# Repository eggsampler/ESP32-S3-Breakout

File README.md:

View this project on [CADLAB.io](https://cadlab.io/project/26428). 

# ESP32-S3-Breakout-
A minimal breakout board for the ESP32-S3-WROOM module

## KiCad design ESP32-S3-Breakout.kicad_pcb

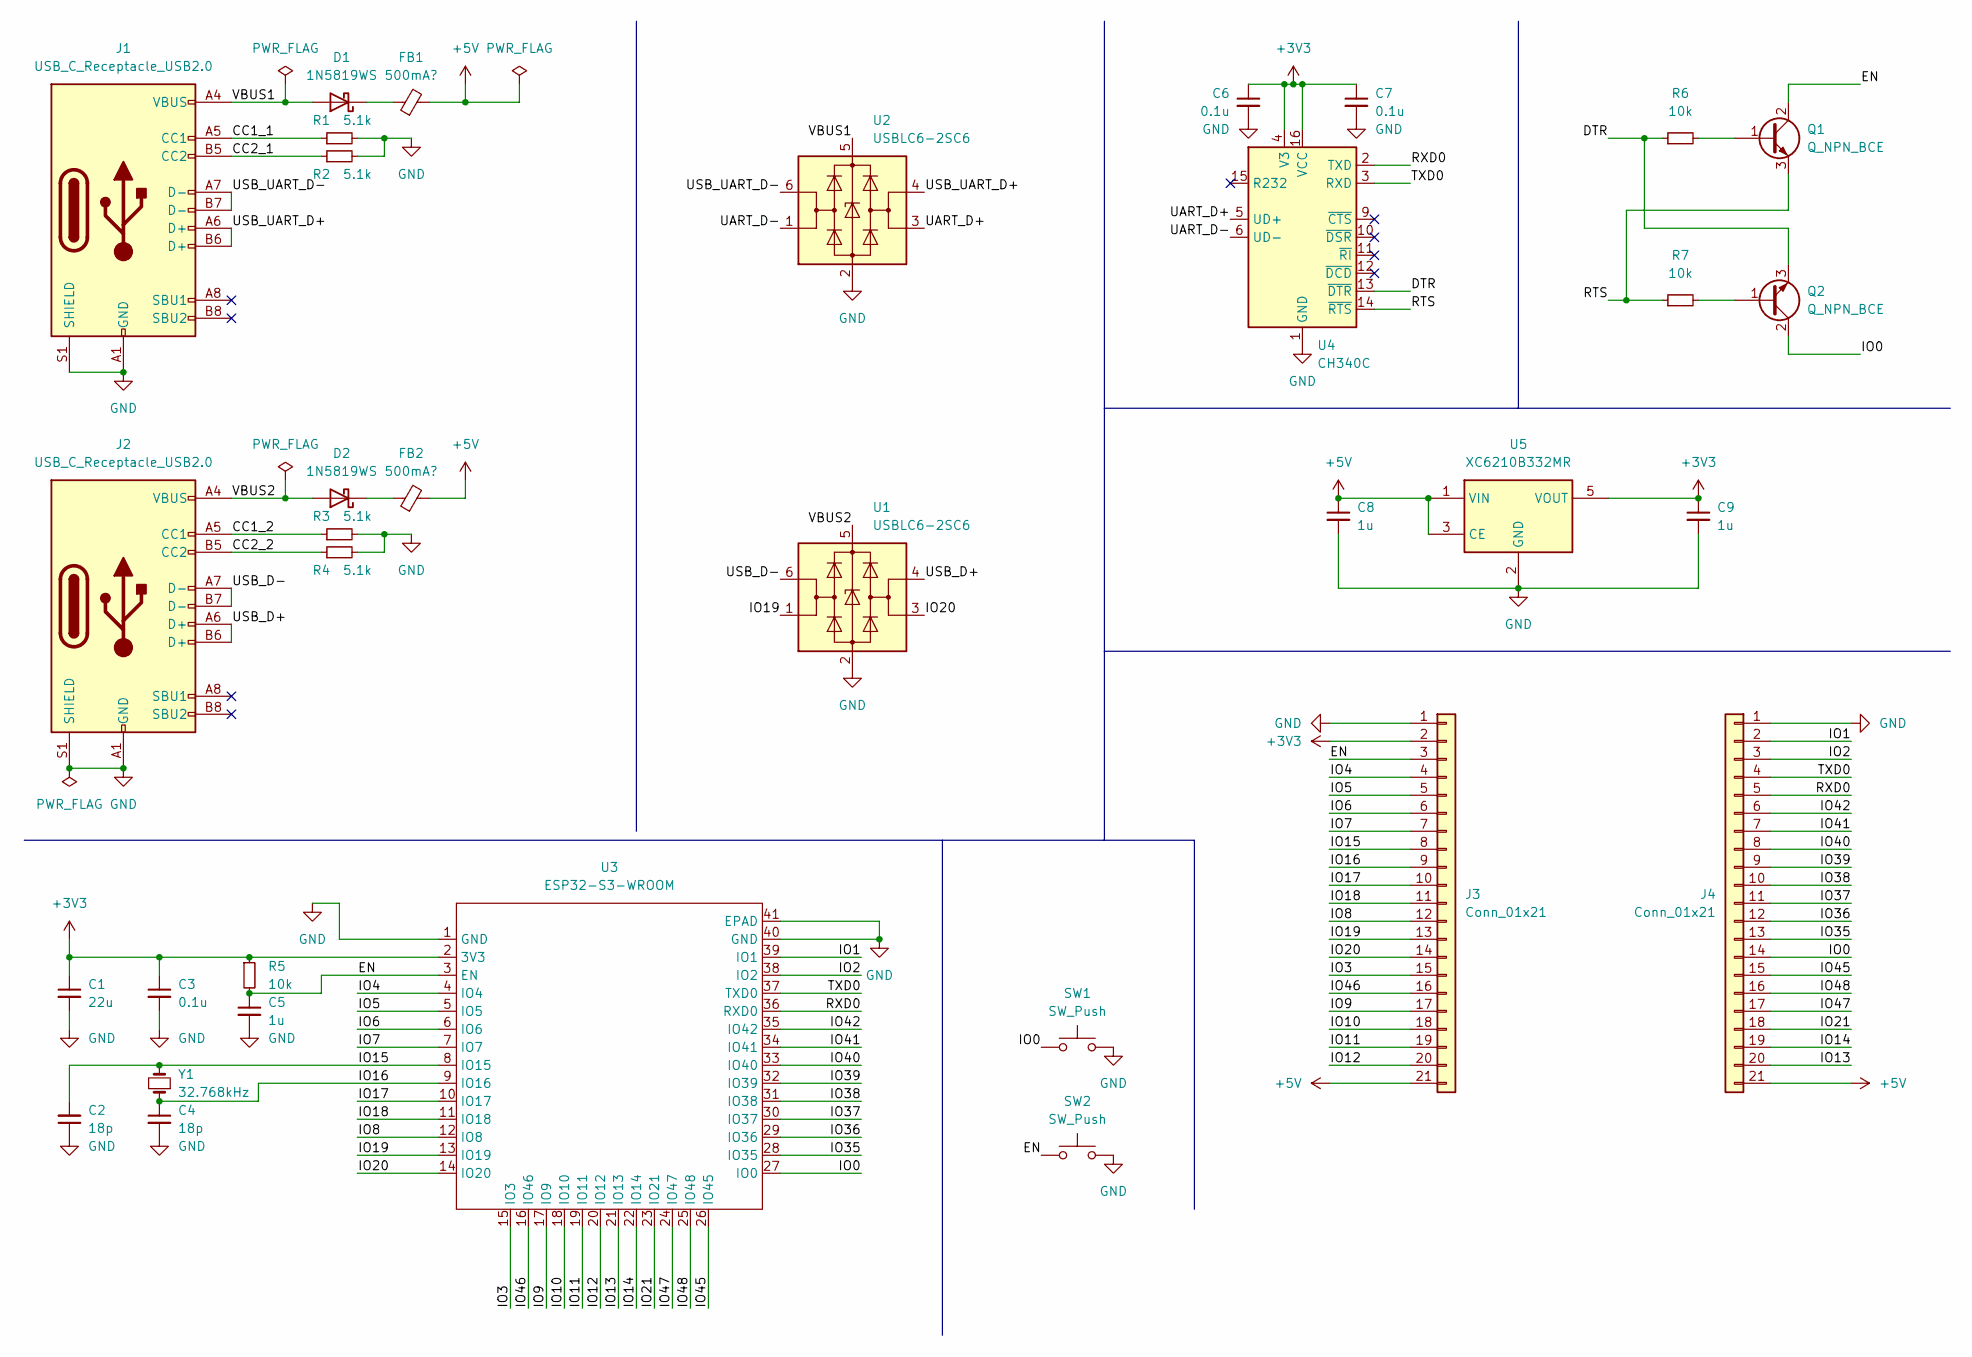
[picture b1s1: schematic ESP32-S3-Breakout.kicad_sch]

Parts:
C1: 22u; C_0805_2012Metric
C2, C4: 18p; C_0603_1608Metric
C3, C6, C7: 0.1u; C_0603_1608Metric
C5: 1u; C_0603_1608Metric
C8, C9: 1u; C_0805_2012Metric
D1, D2: 1N5819WS; D_SOD-323
FB1, FB2: 500mA?; L_0603_1608Metric
J1, J2: USB_C_Receptacle_USB2.0; USB_C_Receptacle_HRO_TYPE-C-31-M-12; LCSC C165948
J3, J4: Conn_01x21; PinHeader_1x21_P2.54mm_Vertical
Q1, Q2: Q_NPN_BCE; SOT-23
R1, R2, R3, R4: 5.1k; R_0603_1608Metric; LCSC C105580
R5, R6, R7: 10k; R_0603_1608Metric
SW1, SW2: SW_Push; SW_SPST_B3U-1000P
U1, U2: USBLC6-2SC6; SOT-23-6
U3: ESP32-S3-WROOM; ESP32-S3-WROOM-1
U4: CH340C; SOIC-16_3.9x9.9mm_P1.27mm
U5: XC6210B332MR; SOT-23-5
Y1: 32.768kHz; Crystal_SMD_3215-2Pin_3.2x1.5mm

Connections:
+3V3: C1.1, C3.1, C6.1, C7.1, C9.1, J3.2, R5.1, U3.2 (3V3), U4.4 (V3), U4.16 (VCC), U5.5 (VOUT)
+5V: C8.1, FB1.2, FB2.2, J3.21, J4.21, U5.1 (VIN), U5.3 (CE)
/CC1_1: J1.A5 (CC1), R1.1
/CC1_2: J2.A5 (CC1), R3.1
/CC2_1: J1.B5 (CC2), R2.1
/CC2_2: J2.B5 (CC2), R4.1
/DTR: Q2.3 (E), R6.1, U4.13 (~DTR)
/EN: C5.1, J3.3, Q1.2 (C), R5.2, SW2.1, U3.3 (EN)
/IO0: J4.14, Q2.2 (C), SW1.1, U3.27 (IO0)
/IO1: J4.2, U3.39 (IO1)
/IO2: J4.3, U3.38 (IO2)
/IO3: J3.15, U3.15 (IO3)
/IO4: J3.4, U3.4 (IO4)
/IO5: J3.5, U3.5 (IO5)
/IO6: J3.6, U3.6 (IO6)
/IO7: J3.7, U3.7 (IO7)
/IO8: J3.12, U3.12 (IO8)
/IO9: J3.17, U3.17 (IO9)
/IO10: J3.18, U3.18 (IO10)
/IO11: J3.19, U3.19 (IO11)
/IO12: J3.20, U3.20 (IO12)
/IO13: J4.20, U3.21 (IO13)
/IO14: J4.19, U3.22 (IO14)
/IO15: C2.2, J3.8, U3.8 (IO15), Y1.2
/IO16: C4.1, J3.9, U3.9 (IO16), Y1.1
/IO17: J3.10, U3.10 (IO17)
/IO18: J3.11, U3.11 (IO18)
/IO19: J3.13, U1.1 (I/O1), U3.13 (IO19)
/IO20: J3.14, U1.3 (I/O2), U3.14 (IO20)
/IO21: J4.18, U3.23 (IO21)
/IO35: J4.13, U3.28 (IO35)
/IO36: J4.12, U3.29 (IO36)
/IO37: J4.11, U3.30 (IO37)
/IO38: J4.10, U3.31 (IO38)
/IO39: J4.9, U3.32 (IO39)
/IO40: J4.8, U3.33 (IO40)
/IO41: J4.7, U3.34 (IO41)
/IO42: J4.6, U3.35 (IO42)
/IO45: J4.15, U3.26 (IO45)
/IO46: J3.16, U3.16 (IO46)
/IO47: J4.17, U3.24 (IO47)
/IO48: J4.16, U3.25 (IO48)
/RTS: Q1.3 (E), R7.1, U4.14 (~RTS)
/RXD0: J4.5, U3.36 (RXD0), U4.2 (TXD)
/TXD0: J4.4, U3.37 (TXD0), U4.3 (RXD)
/UART_D+: U2.3 (I/O2), U4.5 (UD+)
/UART_D-: U2.1 (I/O1), U4.6 (UD-)
/USB_D+: J2.A6 (D+), J2.B6 (D+), U1.4 (I/O2)
/USB_D-: J2.A7 (D-), J2.B7 (D-), U1.6 (I/O1)
/USB_UART_D+: J1.A6 (D+), J1.B6 (D+), U2.4 (I/O2)
/USB_UART_D-: J1.A7 (D-), J1.B7 (D-), U2.6 (I/O1)
/VBUS1: D1.2 (A), J1.A4 (VBUS), J1.A9 (VBUS), J1.B4 (VBUS), J1.B9 (VBUS), U2.5 (VBUS)
/VBUS2: D2.2 (A), J2.A4 (VBUS), J2.A9 (VBUS), J2.B4 (VBUS), J2.B9 (VBUS), U1.5 (VBUS)
GND: C1.2, C2.1, C3.2, C4.2, C5.2, C6.2, C7.2, C8.2, C9.2, J1.A1 (GND), J1.A12 (GND), J1.B1 (GND), J1.B12 (GND), J1.S1 (SHIELD), J2.A1 (GND), J2.A12 (GND), J2.B1 (GND), J2.B12 (GND), J2.S1 (SHIELD), J3.1, J4.1, R1.2, R2.2, R3.2, R4.2, SW1.2, SW2.2, U1.2 (GND), U2.2 (GND), U3.1 (GND), U3.40 (GND), U3.41 (EPAD), U4.1 (GND), U5.2 (GND)
unnamed: D1.1 (K), FB1.1
unnamed: D2.1 (K), FB2.1
unnamed: Q1.1 (B), R6.2
unnamed: Q2.1 (B), R7.2

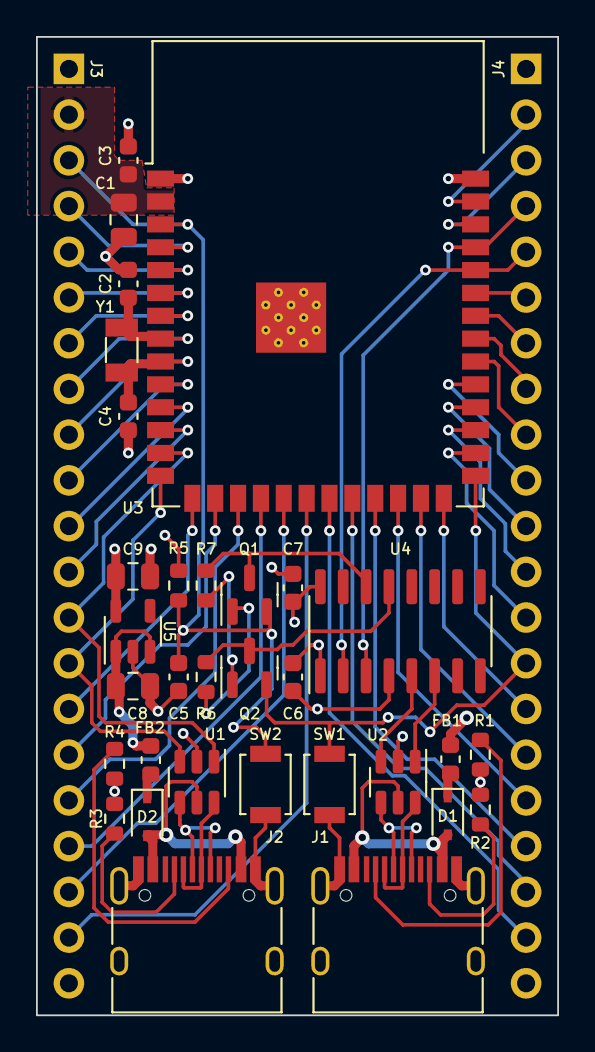
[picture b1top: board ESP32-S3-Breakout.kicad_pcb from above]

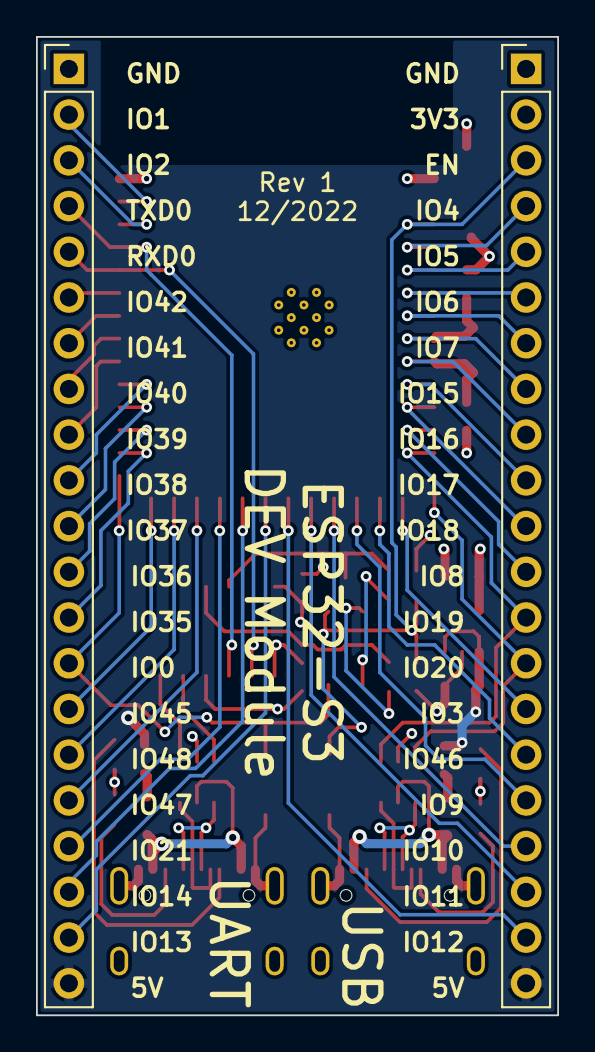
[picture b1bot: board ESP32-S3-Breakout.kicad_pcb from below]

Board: 4 copper layers, 29.0 x 54.4 mm, 34 parts (2 on the bottom side), 58 nets.

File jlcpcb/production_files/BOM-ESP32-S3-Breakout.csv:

Comment,Designator,Footprint,LCSC
0.1u,"C3,C6,C7",C_0603_1608Metric,C14663
1u,C5,C_0603_1608Metric,C15849
18p,"C2,C4",C_0603_1608Metric,C1647
USB_C_Receptacle_USB2.0,"J1,J2",USB_C_Receptacle_HRO_TYPE-C-31-M-12,C165948
1N5819WS,"D1,D2",D_SOD-323,C191023
Q_NPN_BCE,"Q1,Q2",SOT-23,C2146
SW_Push,"SW1,SW2",SW_SPST_B3U-1000P,C231329
5.1k,"R1,R2,R3,R4",R_0603_1608Metric,C23186
10k,"R5,R6,R7",R_0603_1608Metric,C25804
USBLC6-2SC6,"U1,U2",SOT-23-6,C2827654
1u,"C8,C9",C_0805_2012Metric,C28323
ESP32-S3-WROOM,U3,ESP32-S3-WROOM-1,C2913199
32.768kHz,Y1,Crystal_SMD_3215-2Pin_3.2x1.5mm,C32346
XC6210B332MR,U5,SOT-23-5,C424705
22u,C1,C_0805_2012Metric,C45783
500mA?,"FB1,FB2",L_0603_1608Metric,C82155
CH340C,U4,SOIC-16_3.9x9.9mm_P1.27mm,C84681

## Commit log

2023-01-23 Backlink to CADLAB.io has been added.
